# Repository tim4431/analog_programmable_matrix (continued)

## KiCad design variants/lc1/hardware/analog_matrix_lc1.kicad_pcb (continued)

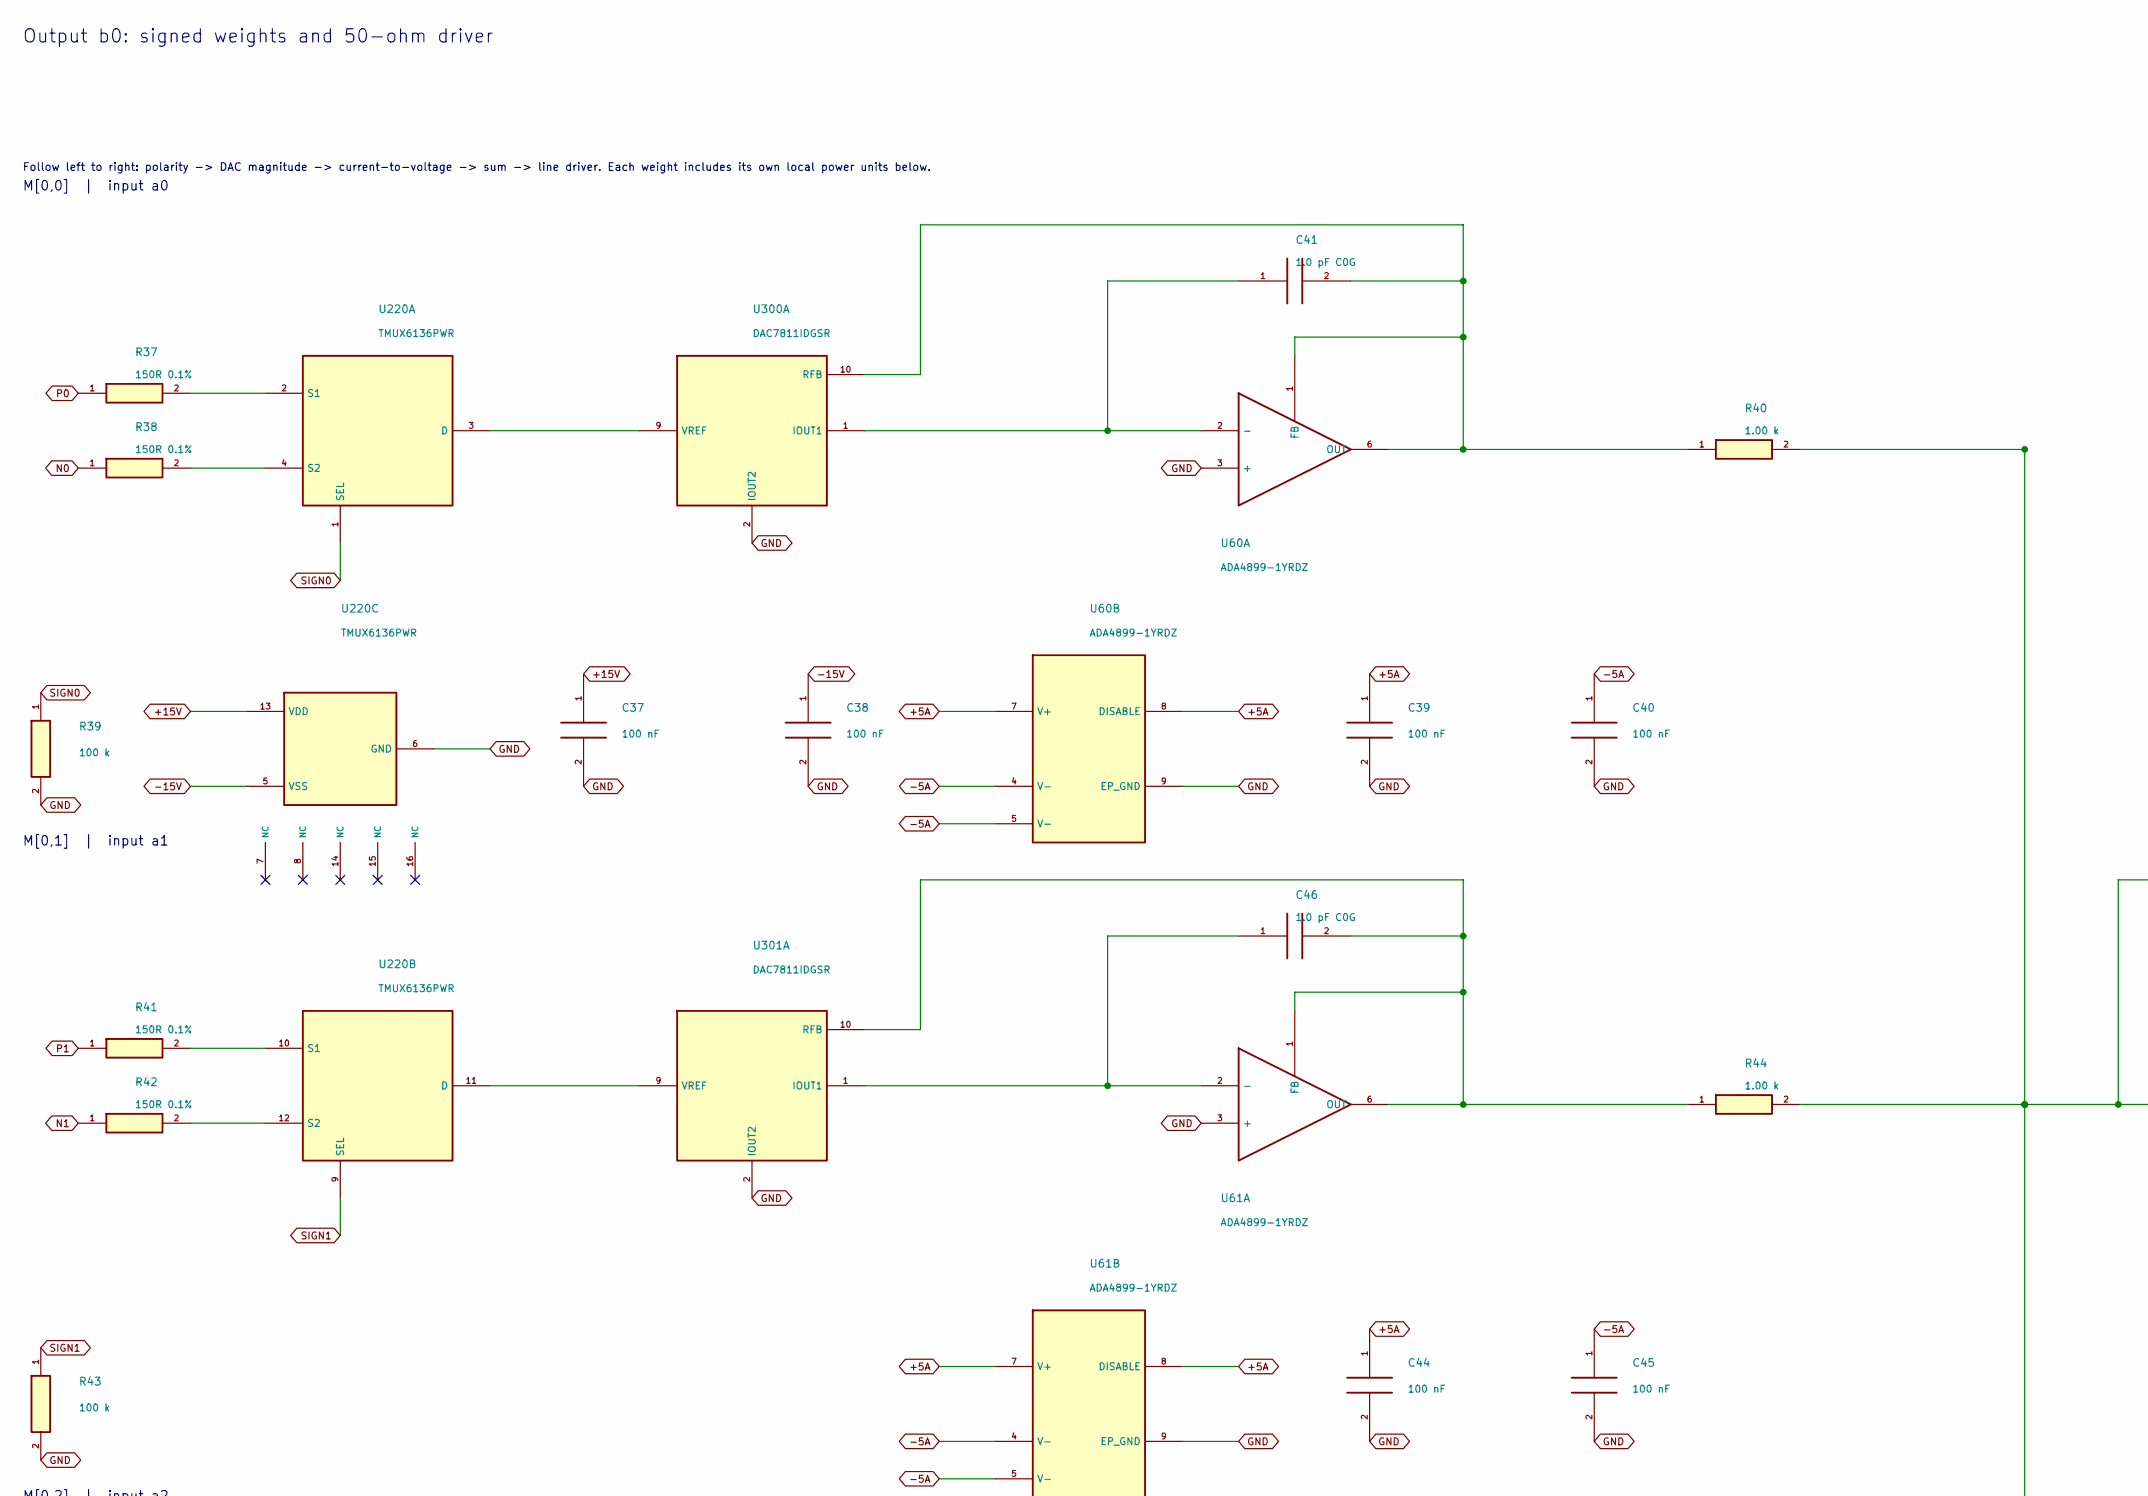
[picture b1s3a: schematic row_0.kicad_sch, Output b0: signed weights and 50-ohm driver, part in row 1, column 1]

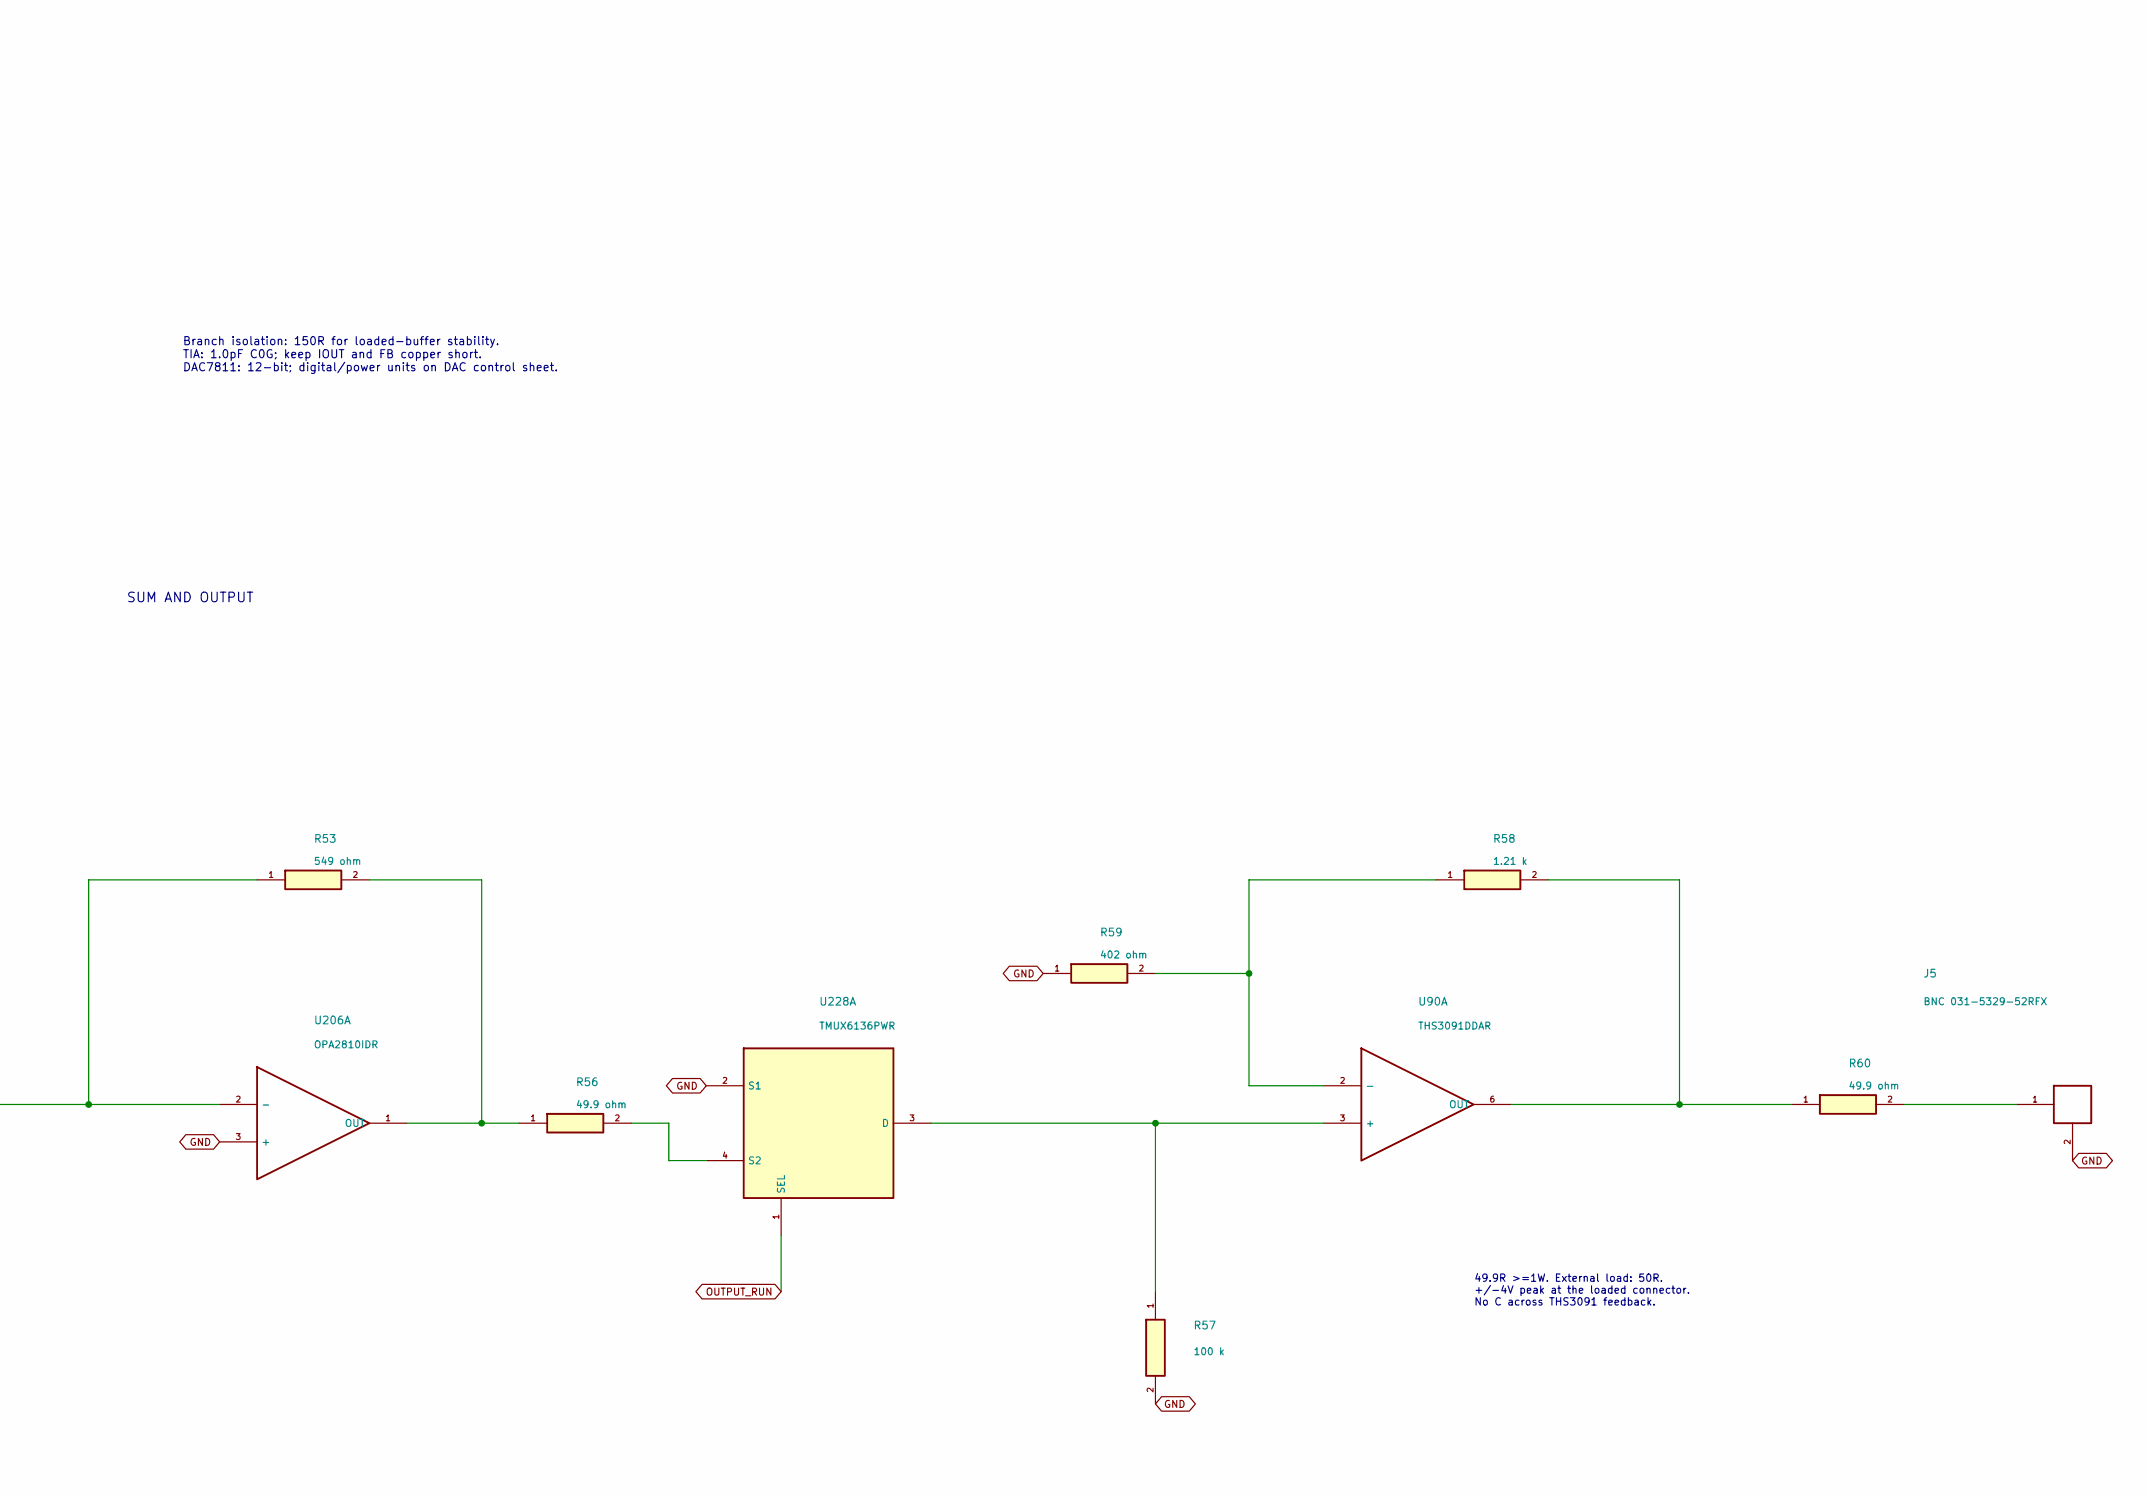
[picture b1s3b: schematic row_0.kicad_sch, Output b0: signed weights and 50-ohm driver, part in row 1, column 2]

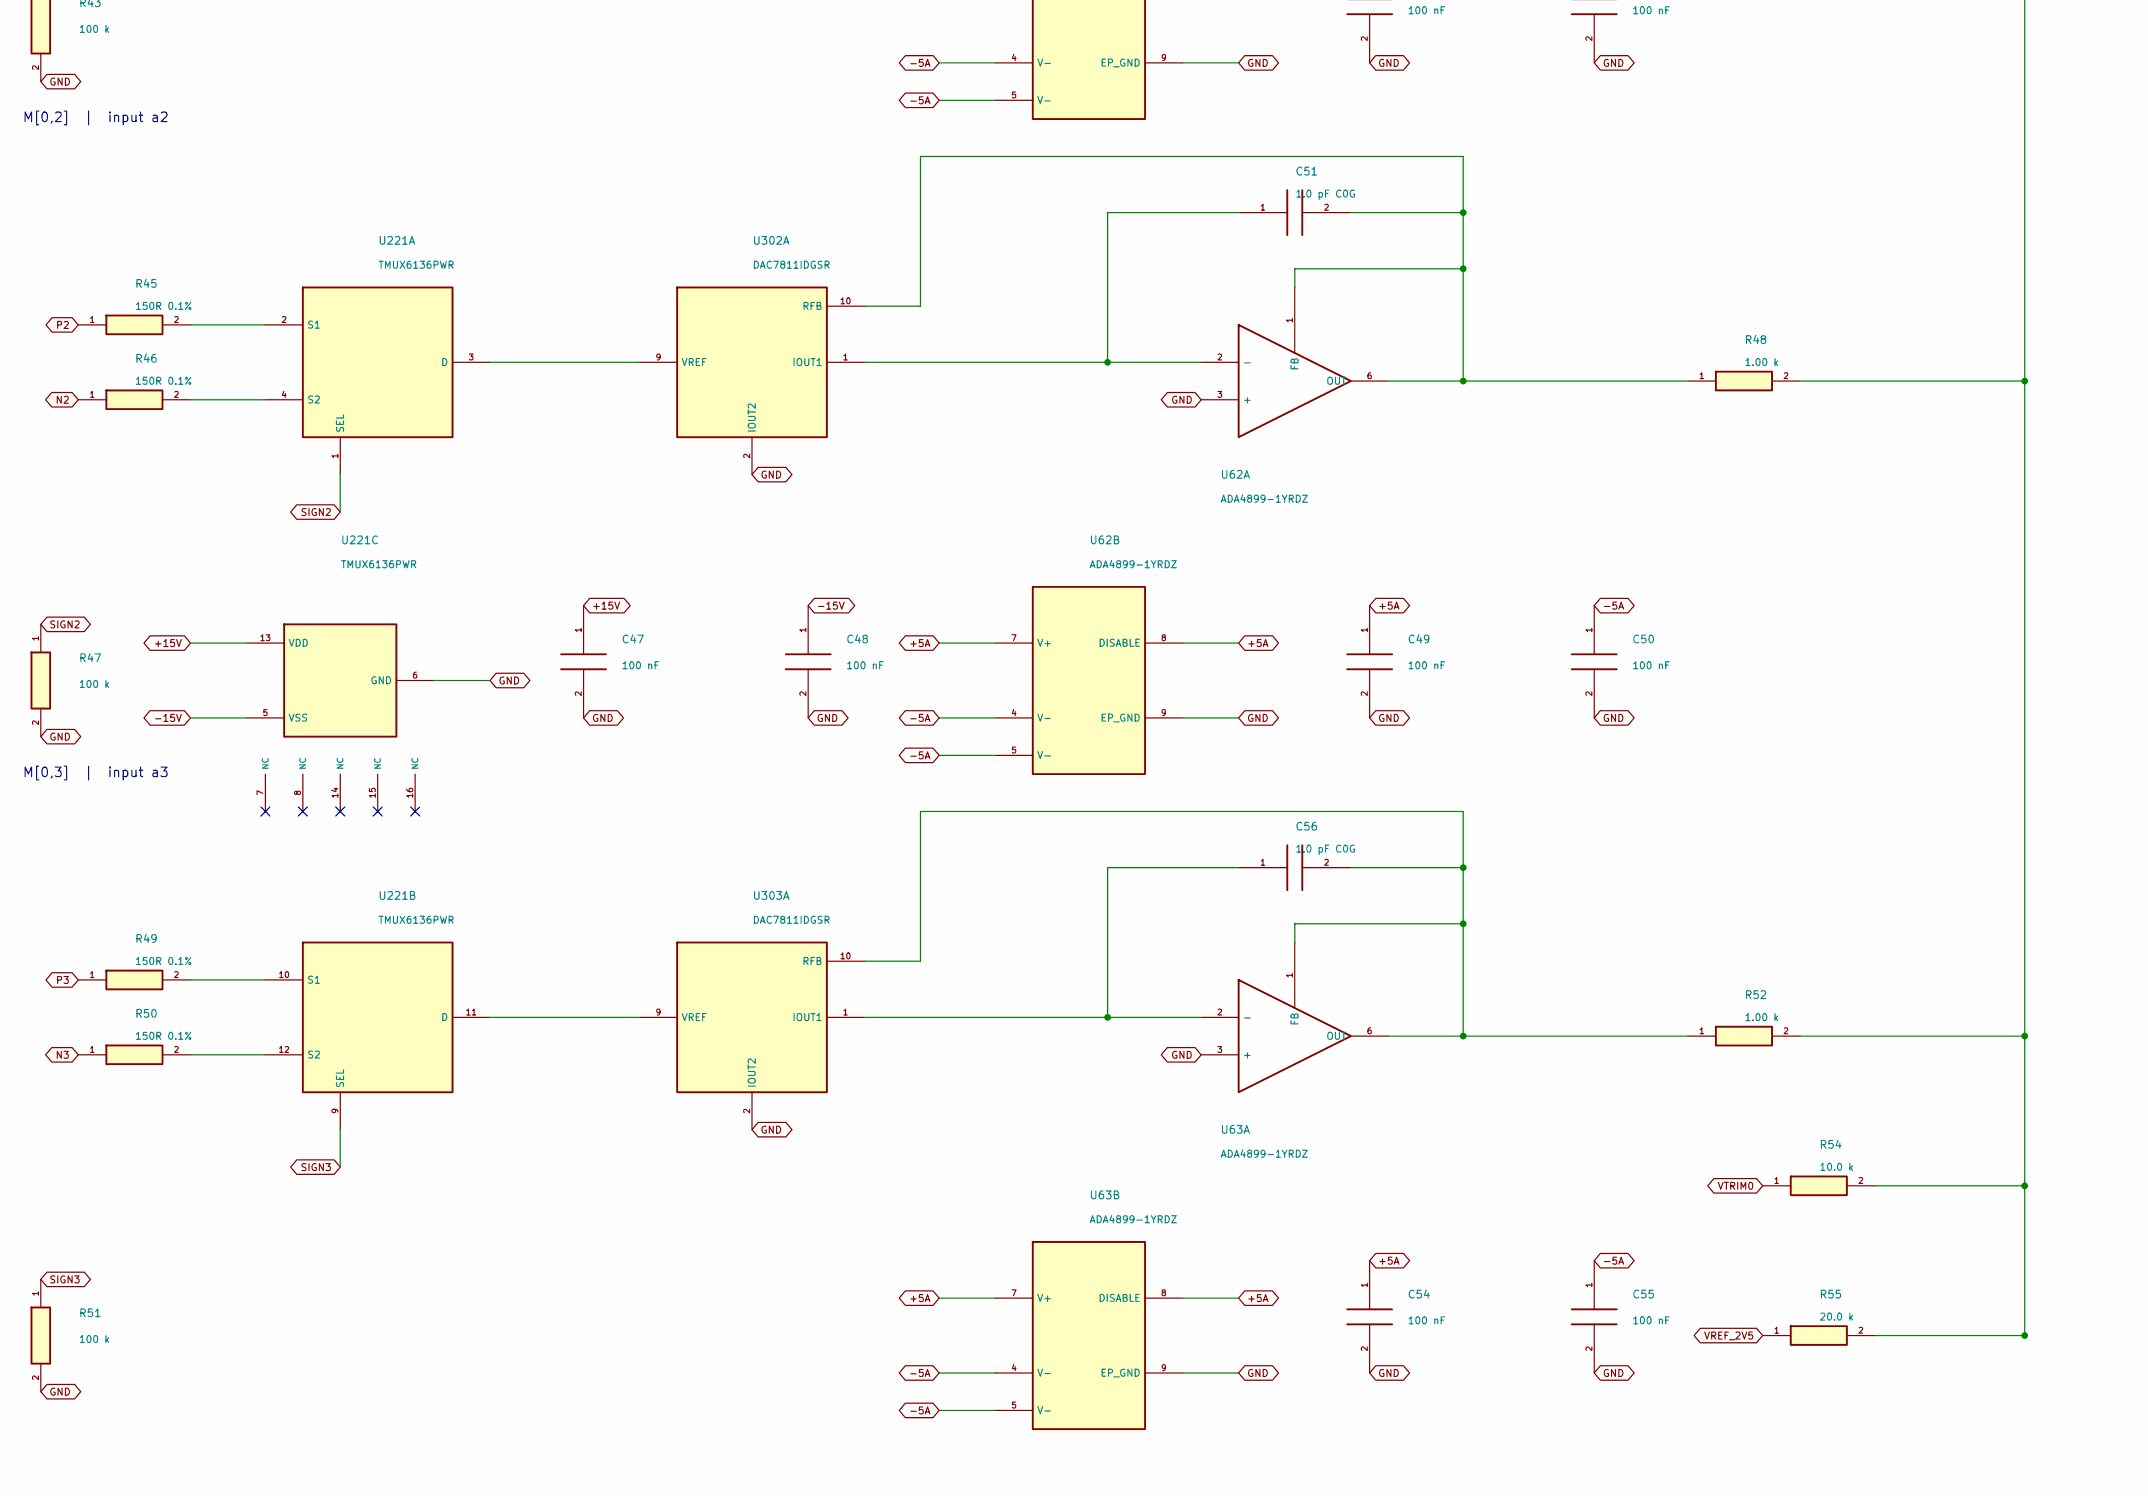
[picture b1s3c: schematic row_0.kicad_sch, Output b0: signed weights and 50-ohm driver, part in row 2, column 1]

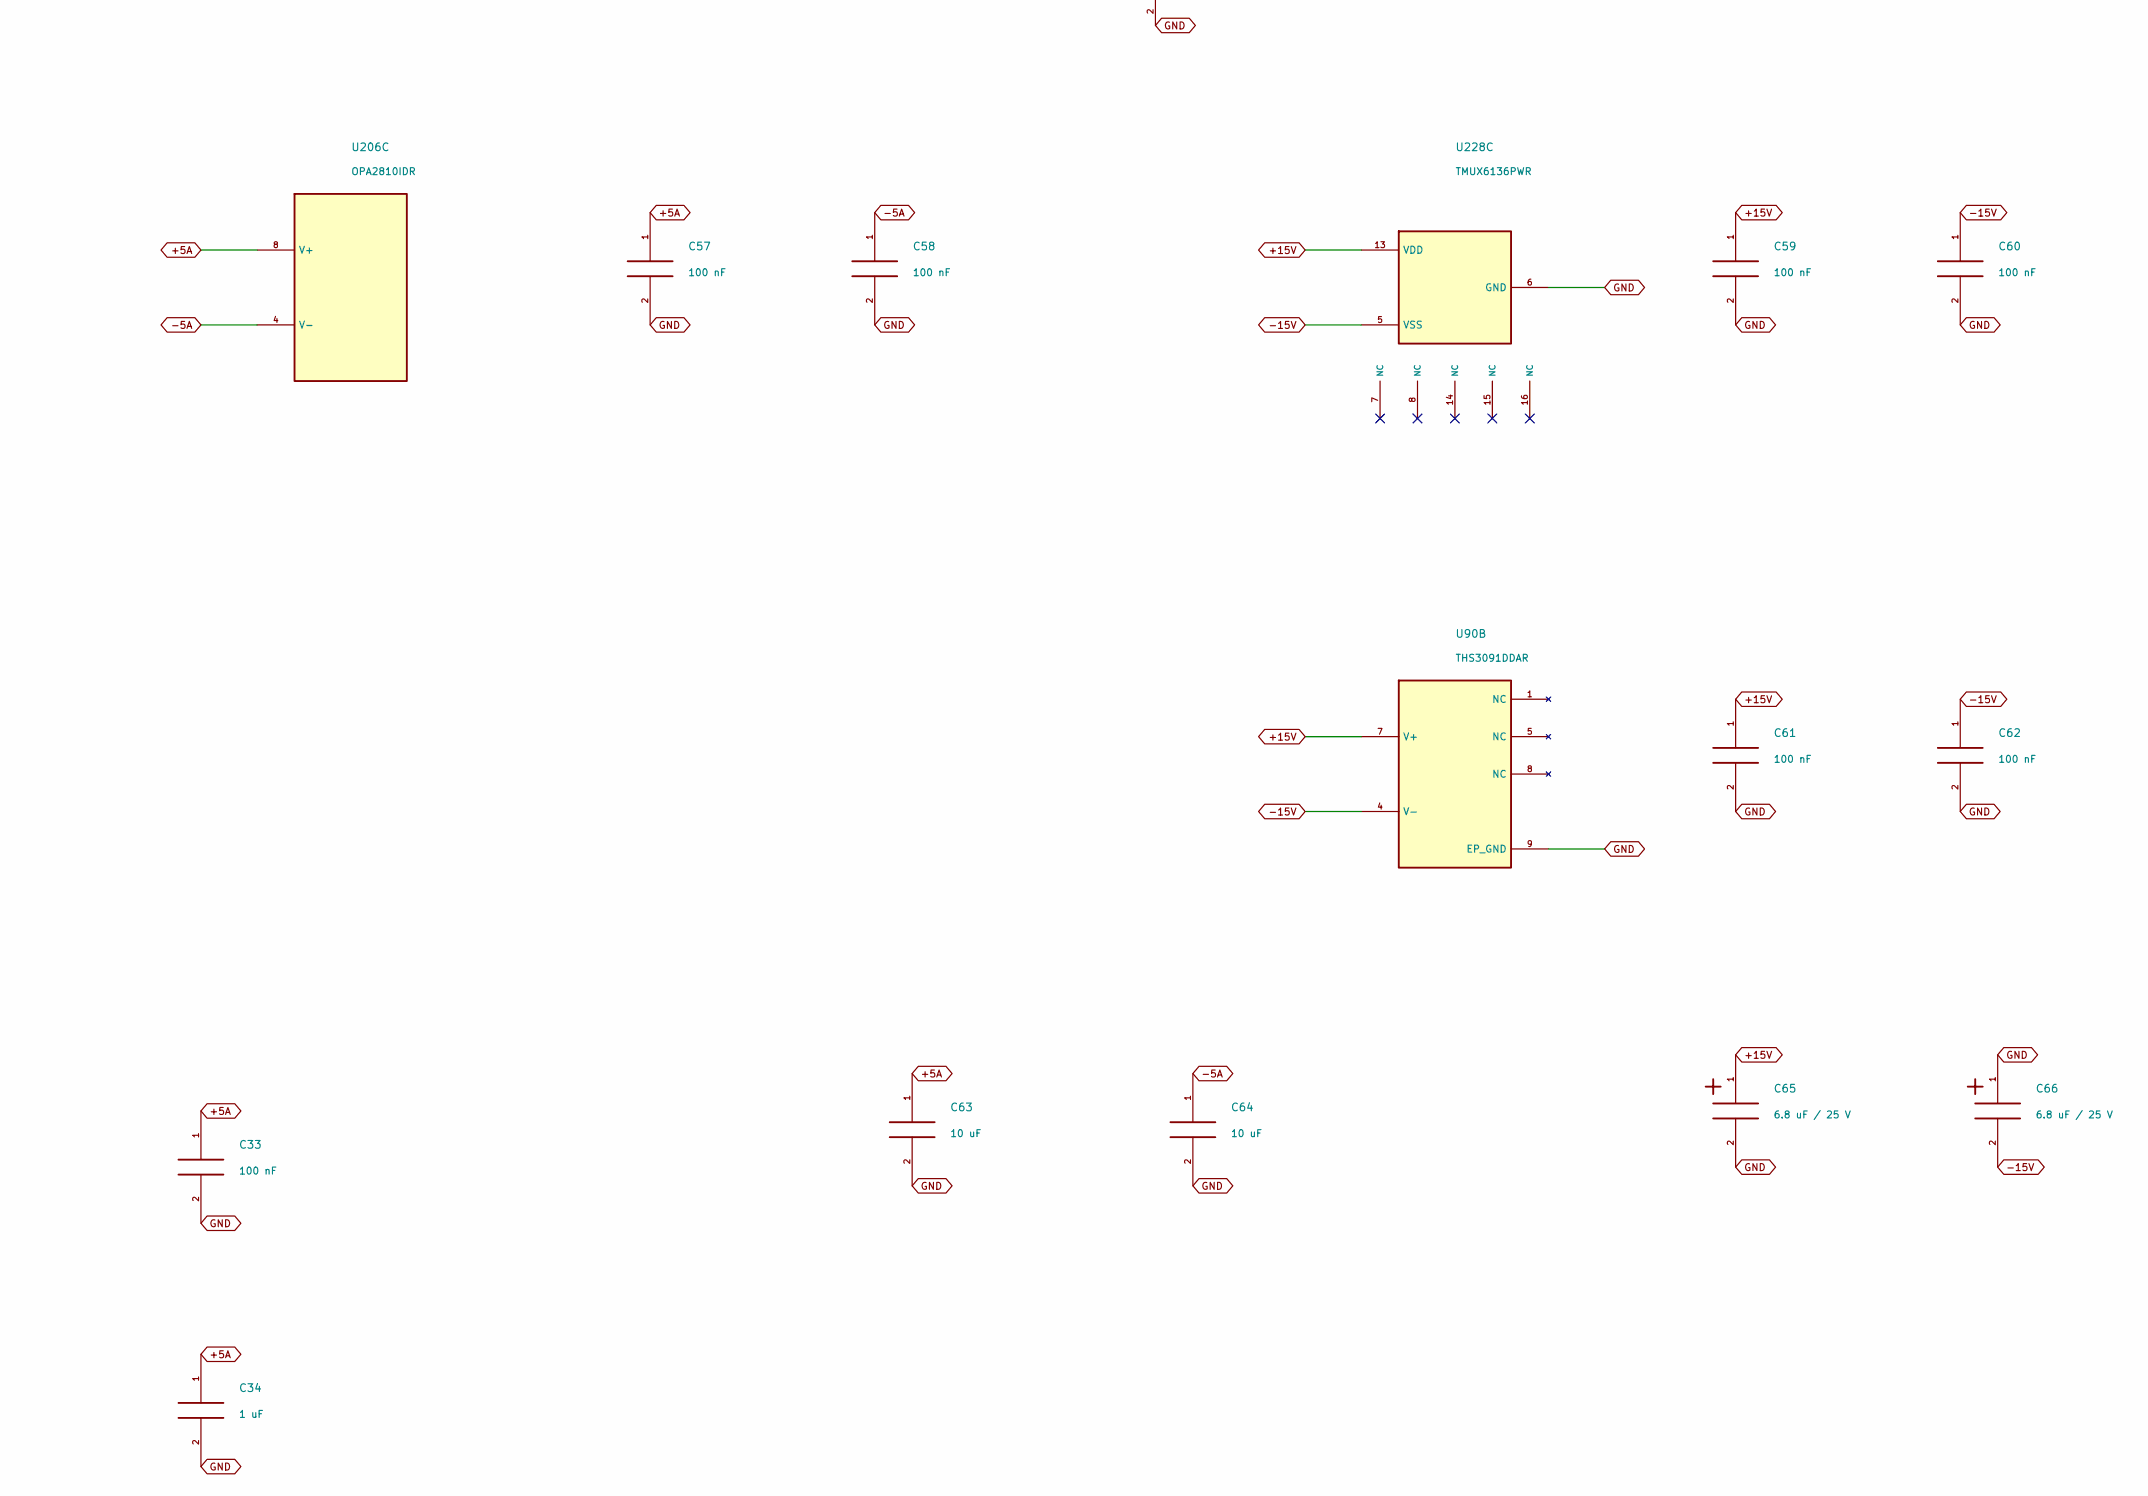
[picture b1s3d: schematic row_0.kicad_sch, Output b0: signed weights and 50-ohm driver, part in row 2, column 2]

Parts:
C33, C37, C38, C39, C40, C44, C45, C47, C48, C49, C50, C54, C55, C57, C58, C59, C60, C61, C62: 100 nF; C_0603_1608Metric; Rating 25V X7R minimum; effective C after bias
C34: 1 uF; C_0805_2012Metric; Rating 25V X7R minimum; effective C after bias
C41, C46, C51, C56: 1.0 pF C0G; C_0402_1005Metric; Rating 50V C0G, +/-0.1pF; stray capacitance in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
C63, C64: 10 uF; C_0805_2012Metric; Rating 25V X7R minimum; effective C after bias
C65, C66: 6.8 uF / 25 V; CP_EIA-3216-18_Kemet-A; Rating 25V polarized
J5: BNC 031-5329-52RFX; BNC_Amphenol_031-5329-52RFX_Vertical
R37, R38, R41, R42, R45, R46, R49, R50: 150R 0.1%; R_0603_1608Metric; Rating 0.1%, <=25ppm/C; 0.1W minimum
R39, R43, R47, R51, R57: 100 k; R_0603_1608Metric; Rating 0.1%, <=25ppm/C; 0.1W minimum
R40, R44, R48, R52: 1.00 k; R_0603_1608Metric; Rating 0.1%, <=25ppm/C; 0.1W minimum
R53: 549 ohm; R_0603_1608Metric; Rating 0.1%, <=25ppm/C; 0.1W minimum
R54: 10.0 k; R_0603_1608Metric; Rating 0.1%, <=25ppm/C; 0.1W minimum
R55: 20.0 k; R_0603_1608Metric; Rating 0.1%, <=25ppm/C; 0.1W minimum
R56: 49.9 ohm; R_0603_1608Metric; Rating 0.1%, <=25ppm/C; 0.1W minimum
R58: 1.21 k; R_0603_1608Metric; Rating 0.1%, <=25ppm/C; 0.1W minimum
R59: 402 ohm; R_0603_1608Metric; Rating 0.1%, <=25ppm/C; 0.1W minimum
R60: 49.9 ohm; R_2512_6332Metric; Rating 0.1%, <=25ppm/C; >=1W
U60, U61, U62, U63: ADA4899-1YRDZ; ADA4899_RD8_EP2.29x2.29
U90: THS3091DDAR; SOIC-8-1EP_3.9x4.9mm_P1.27mm_EP2.95x4.9mm_Mask2.71x3.4mm_Th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
U206: OPA2810IDR; SOIC-8_3.9x4.9mm_P1.27mm
U220, U221, U228: TMUX6136PWR; TSSOP-16_4.4x5mm_P0.65mm
U300, U301, U302, U303: DAC7811IDGSR; VSSOP-10_3x3mm_P0.5mm

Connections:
+5A: C33.1, C34.1, C39.1, C44.1, C49.1, C54.1, C57.1, C63.1, U60.7 (V+), U60.8 (DISABLE), U61.7 (V+), U61.8 (DISABLE), U62.7 (V+), U62.8 (DISABLE), U63.7 (V+), U63.8 (DISABLE), U206.8 (V+); also elsewhere on the board
+15V: C37.1, C47.1, C59.1, C61.1, C65.1, U90.7 (V+), U220.13 (VDD), U221.13 (VDD), U228.13 (VDD); also elsewhere on the board
-5A: C40.1, C45.1, C50.1, C55.1, C58.1, C64.1, U60.4 (V-), U60.5 (V-), U61.4 (V-), U61.5 (V-), U62.4 (V-), U62.5 (V-), U63.4 (V-), U63.5 (V-), U206.4 (V-); also elsewhere on the board
-15V: C38.1, C48.1, C60.1, C62.1, C66.2, U90.4 (V-), U220.5 (VSS), U221.5 (VSS), U228.5 (VSS); also elsewhere on the board
GND: C33.2, C34.2, C37.2, C38.2, C39.2, C40.2, C44.2, C45.2, C47.2, C48.2, C49.2, C50.2, C54.2, C55.2, C57.2, C58.2, C59.2, C60.2, C61.2, C62.2, C63.2, C64.2, C65.2, C66.1, J5.2, R39.2, R43.2, R47.2, R51.2, R57.2, R59.1, U60.3 (+), U60.9 (EP_GND), U61.3 (+), U61.9 (EP_GND), U62.3 (+), U62.9 (EP_GND), U63.3 (+), U63.9 (EP_GND), U90.9 (EP_GND), U206.3 (+), U220.6 (GND), U221.6 (GND), U228.2 (S1), U228.6 (GND), U300.2 (IOUT2), U301.2 (IOUT2), U302.2 (IOUT2), U303.2 (IOUT2); also elsewhere on the board
N0: R38.1; also elsewhere on the board
N1: R42.1; also elsewhere on the board
N2: R46.1; also elsewhere on the board
N3: R50.1; also elsewhere on the board
unnamed: J5.1, R60.2
unnamed: R58.1, R59.2, U90.2 (-)
unnamed: R58.2, R60.1, U90.6 (OUT)
unnamed: R40.2, R44.2, R48.2, R52.2, R53.1, R54.2, R55.2, U206.2 (-)
unnamed: R53.2, R56.1, U206.1 (OUT)
unnamed: U220.3 (D), U300.9 (VREF)
unnamed: R37.2, U220.2 (S1)
unnamed: R38.2, U220.4 (S2)
unnamed: U220.11 (D), U301.9 (VREF)
unnamed: R41.2, U220.10 (S1)
unnamed: R42.2, U220.12 (S2)
unnamed: U221.3 (D), U302.9 (VREF)
unnamed: R45.2, U221.2 (S1)
unnamed: R46.2, U221.4 (S2)
unnamed: U221.11 (D), U303.9 (VREF)
unnamed: R49.2, U221.10 (S1)
unnamed: R50.2, U221.12 (S2)
unnamed: R57.1, U90.3 (+), U228.3 (D)
unnamed: R56.2, U228.4 (S2)
unnamed: C41.1, U60.2 (-), U300.1 (IOUT1)
unnamed: C41.2, R40.1, U60.1 (FB), U60.6 (OUT), U300.10 (RFB)
unnamed: C46.1, U61.2 (-), U301.1 (IOUT1)
unnamed: C46.2, R44.1, U61.1 (FB), U61.6 (OUT), U301.10 (RFB)
unnamed: C51.1, U62.2 (-), U302.1 (IOUT1)
unnamed: C51.2, R48.1, U62.1 (FB), U62.6 (OUT), U302.10 (RFB)
unnamed: C56.1, U63.2 (-), U303.1 (IOUT1)
unnamed: C56.2, R52.1, U63.1 (FB), U63.6 (OUT), U303.10 (RFB)
OUTPUT_RUN: U228.1 (SEL); also elsewhere on the board
P0: R37.1; also elsewhere on the board
P1: R41.1; also elsewhere on the board
P2: R45.1; also elsewhere on the board
P3: R49.1; also elsewhere on the board
SIGN0: R39.1, U220.1 (SEL); also elsewhere on the board
SIGN1: R43.1, U220.9 (SEL); also elsewhere on the board
SIGN2: R47.1, U221.1 (SEL); also elsewhere on the board
SIGN3: R51.1, U221.9 (SEL); also elsewhere on the board
VREF_2V5: R55.1; also elsewhere on the board
VTRIM0: R54.1; also elsewhere on the board

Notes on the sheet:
Output b0: signed weights and 50-ohm driver
Follow left to right: polarity -> DAC magnitude -> current-to-voltage -> sum -> line driver. Each weight includes its own local power units below.
M[0,0] | input a0
M[0,1] | input a1
M[0,2] | input a2
M[0,3] | input a3
SUM AND OUTPUT
49.9R >=1W. External load: 50R. +/-4V peak at the loaded connector. No C across THS3091 feedback.
Branch isolation: 150R for loaded-buffer stability. TIA: 1.0pF C0G; keep IOUT and FB copper short. DAC7811: 12-bit; digital/power units on DAC control sheet.
